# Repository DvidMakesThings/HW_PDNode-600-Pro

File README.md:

# PDNode-600 Pro  
## High-Performance USB PD Power Distribution Unit – 10" Rackmount

## Description  
[ENERGIS](https://github.com/DvidMakesThings/HW_10-In-Rack_PDU) is the 230V managed PDU project. PDNode-600 Pro is the modular DC/USB-C sibling for setups
where mains switching is not desired, but controllable, rack-friendly power output is still needed.

The PDNode-600 is a professional-grade, 600W USB Power Delivery Unit designed specifically for compact 10-inch rack systems, targeting embedded developers, homelab enthusiasts, test benches, and smart infrastructure. It delivers regulated, high-current power across 8x independent USB-C PD outputs and 4x fixed 5V USB-A outputs.

At the core of the PDNode platform is a centralized industrial-grade 24V/25A power supply, distributing regulated DC to dedicated per-port buck or buck-boost converters. Each USB-C port is managed by an MPQ4242-AEC1 PD controller, enabling clean, autonomous negotiation of power profiles up to 20V @ 3A or 5A with eMarker cable support. All power conversion, protection, and monitoring are designed to meet high reliability and safety standards.

The PDNode-600 Pro, by contrast, is built for remote-managed racks and headless environments, featuring Ethernet connectivity, a clean web-based UI, SNMP integration, and firmware updates via USB-C. Doing this by using [BladeCore-M54E](https://github.com/DvidMakesThings/HW_BladeCore-M54E)

## Web UI sneak peek

Interactive playground (dummy UI):
- https://dvidmakesthings.github.io/HW_PDNode-600-Pro/playground/

## Project timeline estimation

Status legend: ✅ Completed · 🟠 Ongoing · 🔵 Planned

| #  | Milestone                                      | Planned Start | Planned End | Status       | Notes |
|:--:|------------------------------------------------|---------------|-------------|--------------|-------|
| 1  | Architecture definition                        | 12-2025       | 01-2026     | ✅ Completed |       |
| 2  | Baseboard PCB design                           | 15-02-2026    | TBD         | ✅ Completed |       |
| 3  | PD card PCB design                             | 25-02-2026    | TBD         | ✅ Completed |       |
| 4  | Documentation                                  | 12-2025       | 2026.12     | 🟠 Ongoing   |       |
| 5  | PCB ordering                                   | 01-03-2026    | 31-03-2026  | ✅ Completed | Waiting for arrival |
| 6  | Prototyping and hardware bring-up              | 03-2026       | 30-04-2026  | 🟠 Ongoing   |       |
| 7  | Firmware bring-up (slot scan, mux, PD iface)   | 06-2026       | 11-2026     | 🔵 Planned   |       |
| 8  | Telemetry and status reporting                 | 06-2026       | 11-2026     | 🔵 Planned   |       |
| 9  | Validation (load, thermal, long-run)           | 06-2026       | 11-2026     | 🔵 Planned   |       |
| 10 | Integration and polishing                      | 06-2026       | 11-2026     | 🔵 Planned   |       |
| 11 | Release package and final docs                 | 11-2026       | 12-2026     | 🔵 Planned   |       |

## Specifications 

### Input
- **Input voltage:** 230 VAC, max 4A 
- **System topology:** 24V distribution on the baseboard, per-slot conversion on PD cards

### Output (per PD card / per slot)
- **8x independent USB-C PD source**:
  - 5V 3A (5A only with 5A e-marked cable)
  - 9V 3A (5A only with 5A e-marked cable)
  - 12V 3A (5A only with 5A e-marked cable)
  - 15V 3A (5A only with 5A e-marked cable)
  - 20V 3A (5A only with 5A e-marked cable)
  - (Total power output cannot exceed 600W)
- **4x USB-A source** up to **5V / 1A** per port (depending on configuration and limits)

---

## Features
- **8x independent USB-C PD source ports** (modular PD cards, one port per slot)
- **Per-port PD profiles**
- **Total system capability: up to 600W** (shared input power budget)
- **4x USB-A auxiliary outputs** (5V, 1A per port) for low-power devices
- **Ethernet connectivity** for control / monitoring
- **USB service interface** (debug, configuration, firmware update, or log access depending on implementation)
- **Per-port power monitoring** (current/voltage telemetry via onboard sensing)
- **Per-port status reporting** (PGOOD / fault indication, and software-readable status)
- **Hot-swappable slot concept** (cards can be replaced without redesigning the baseboard)

---

## Hardware architecture

### Baseboard
- 24V DC input from industrial power supply
- Power distribution to all slots (high-current bus)
- Slot connectors + slot management (card detect, enable, status aggregation)
- I2C fanout per slot (mux) for monitoring and controlling devices
- Ethernet interface for user interaction
- USB/service interface for debug/config/updates
- 4x USB-A outputs
- 8x USB-C PD outputs

### [BladeCore-M54E](https://github.com/DvidMakesThings/HW_BladeCore-M54E)
- RP2354B microcontroller
- External QSPI flash memory
- External I²C EEPROM
- 100BASE Ethernet via W5500
- Dual‑path USB connectivity with automatic source selection
- Onboard power regulation and defined power‑up sequencing
- Compact M.2 M-key form factor

### PD Card
- 1x USB-C PD source port (one card = one port)
- Local power conversion to generate VBUS from the 24V bus
- PD controller + USB-C port control signals (enable, reset, IRQ)
- Per-port current/voltage measurement
- Per-port power good / fault status output
- Optional ID EEPROM footprint (DNI) for traceability/calibration

## Schematics
The full schematics are available:
- **[Baseboard Schematics](src/PDF/SCH_PDNode_Baseboard_100.pdf)** 
- **[PDCard-4242 Schematics](src/PDF/SCH_PDCard-4242_100.pdf)**
- **[BladeCore-M54E Schematics](src/PDF/SCH_BladeCore-M54_100.pdf)**

PCB Documentation:
- **[Baseboard PCB](src/PDF/PCB_PDNode_Baseboard_100.pdf)** 
- **[PDCard-4242 PCB](src/PDF/PCB_PDCard-4242_100.pdf)**
 ****

---

## Development Phases (Hardware + Firmware)

| Hardware Phase                          | Status          | Firmware Phase                         | Status         |
| --------------------------------------- | --------------- | -------------------------------------- | -------------- |
| Architecture definition                 | ✅ Completed    | Slot scan concept (TCA9548A)           | 🔵 Planned     |
| Baseboard PCB Design                    | ✅ Completed    | I2C driver + mux control               | 🔵 Planned     |
| PD Card PCB Design                      | ✅ Completed    | INA219 monitoring                      | 🔵 Planned     |
| Documentation                           | 🟠 Ongoing      | PD controller interface (SPI + GPIO)   | 🔵 Planned     |
| PCB ordering                            | ✅ Completed    | Telemetry + status reporting           | 🔵 Planned     |
| Prototyping and Hardware Bring-up       | 🟠 Ongoing      | Bring-up scripts / debug tooling       | 🔵 Planned     |
| Validation (load, thermal, long-run)    | 🔵 Planned      | Error handling + fault reporting       | 🔵 Planned     |
| Production optimization                 | 🔵 Planned      | Integration and polishing              | 🔵 Planned     |

---

## Changelog 
#### Rev0.1.0:
- Initial design
- STUSB4710 controller + TPS552882

#### Rev1.0.0:
- Full redesign. STUSB4710 became EOL, need to use different PD controller
- New concept: modular Baseboard + PDCard architecture
- PDCard power stage (MPQ4242-AEC1)
- Baseboard: Per-slot I2C muxing (TCA9548A)
- Optional per-card EEPROM (not used, but capable)

<table>
  <tr>
    <td align="center">
      
      <br><b>PDCard Top</b>
    </td>
    <td align="center">
      
      <br><b>PDCard Bottom</b>
    </td>
  </tr>
  <tr>
    <td align="center" width="50%">
      
      <br><b>BladeCore-M54E Top</b>
    </td>
    <td align="center" width="50%">
      
      <br><b>BladeCore-M54E Bottom</b>
    </td>
  </tr>
  <tr>
    <td align="center">
      
      <br><b>BladeCore-M54E Top</b>
    </td>
    <td align="center">
      
      <br><b>BladeCore-M54E Bottom</b>
    </td>
  </tr>
</table>

## License
### Software Components
This project's software is licensed under the **GNU Affero General Public License v3.0 (AGPL-3.0)**.
See the [Software License](LICENSE-AGPL) file for details.

#### What AGPL-3.0 means:

- ✅ **You can** freely use, modify, and distribute this software
- ✅ **You can** use this project for personal, educational, or internal purposes
- ✅ **You can** contribute improvements back to this project

- ⚠️ **You must** share any modifications you make if you distribute the software
- ⚠️ **You must** release the source code if you run a modified version on a server that others interact with
- ⚠️ **You must** keep all copyright notices intact

- ❌ **You cannot** incorporate this code into proprietary software without sharing your source code
- ❌ **You cannot** use this project in a commercial product without either complying with AGPL or obtaining a different license

### Hardware Components
Hardware designs, schematics, and related documentation are licensed under the **Creative Commons Attribution-NonCommercial-ShareAlike 4.0 International License (CC BY-NC-SA 4.0 International License)**. See the [Hardware License](LICENSE-CC-BY-NC-SA) file for details.

#### What CC BY-NC-SA 4.0 means:

- ✅ **You can** study, modify, and distribute the hardware designs
- ✅ **You can** create derivative works for personal, educational, or non-commercial use
- ✅ **You can** build this project for your own personal use

- ⚠️ **You must** give appropriate credit and indicate if changes were made
- ⚠️ **You must** share any modifications under the same license terms
- ⚠️ **You must** include the original license and copyright notices

- ❌ **You cannot** use the designs for commercial purposes without explicit permission
- ❌ **You cannot** manufacture and sell products based on these designs without a commercial license
- ❌ **You cannot** create closed-source derivatives for commercial purposes
- ❌ **You cannot** use the designer's trademarks without permission

### Commercial & Enterprise Use

Commercial use of this project is prohibited without obtaining a separate commercial license. If you are interested in:

- Manufacturing and selling products based on these designs
- Incorporating these designs into commercial products
- Any other commercial applications

Please contact me through any of the channels listed in the [Contact](#contact) section to discuss commercial licensing arrangements. Commercial licenses are available with reasonable terms to support ongoing development.

## Contact

For questions or feedback:
- **Email:** [dvidmakesthings@gmail.com](mailto:dvidmakesthings@gmail.com)
- **GitHub:** [DvidMakesThings](https://github.com/DvidMakesThings)

## Contributing

Contributions are welcome! As this is an early-stage project, please reach out before 
making substantial changes:

1. Fork the repository
2. Create a feature branch (`git checkout -b feature/concept`)
3. Commit your changes (`git commit -m 'Add concept'`)
4. Push to the branch (`git push origin feature/concept`)
5. Open a Pull Request with a detailed description

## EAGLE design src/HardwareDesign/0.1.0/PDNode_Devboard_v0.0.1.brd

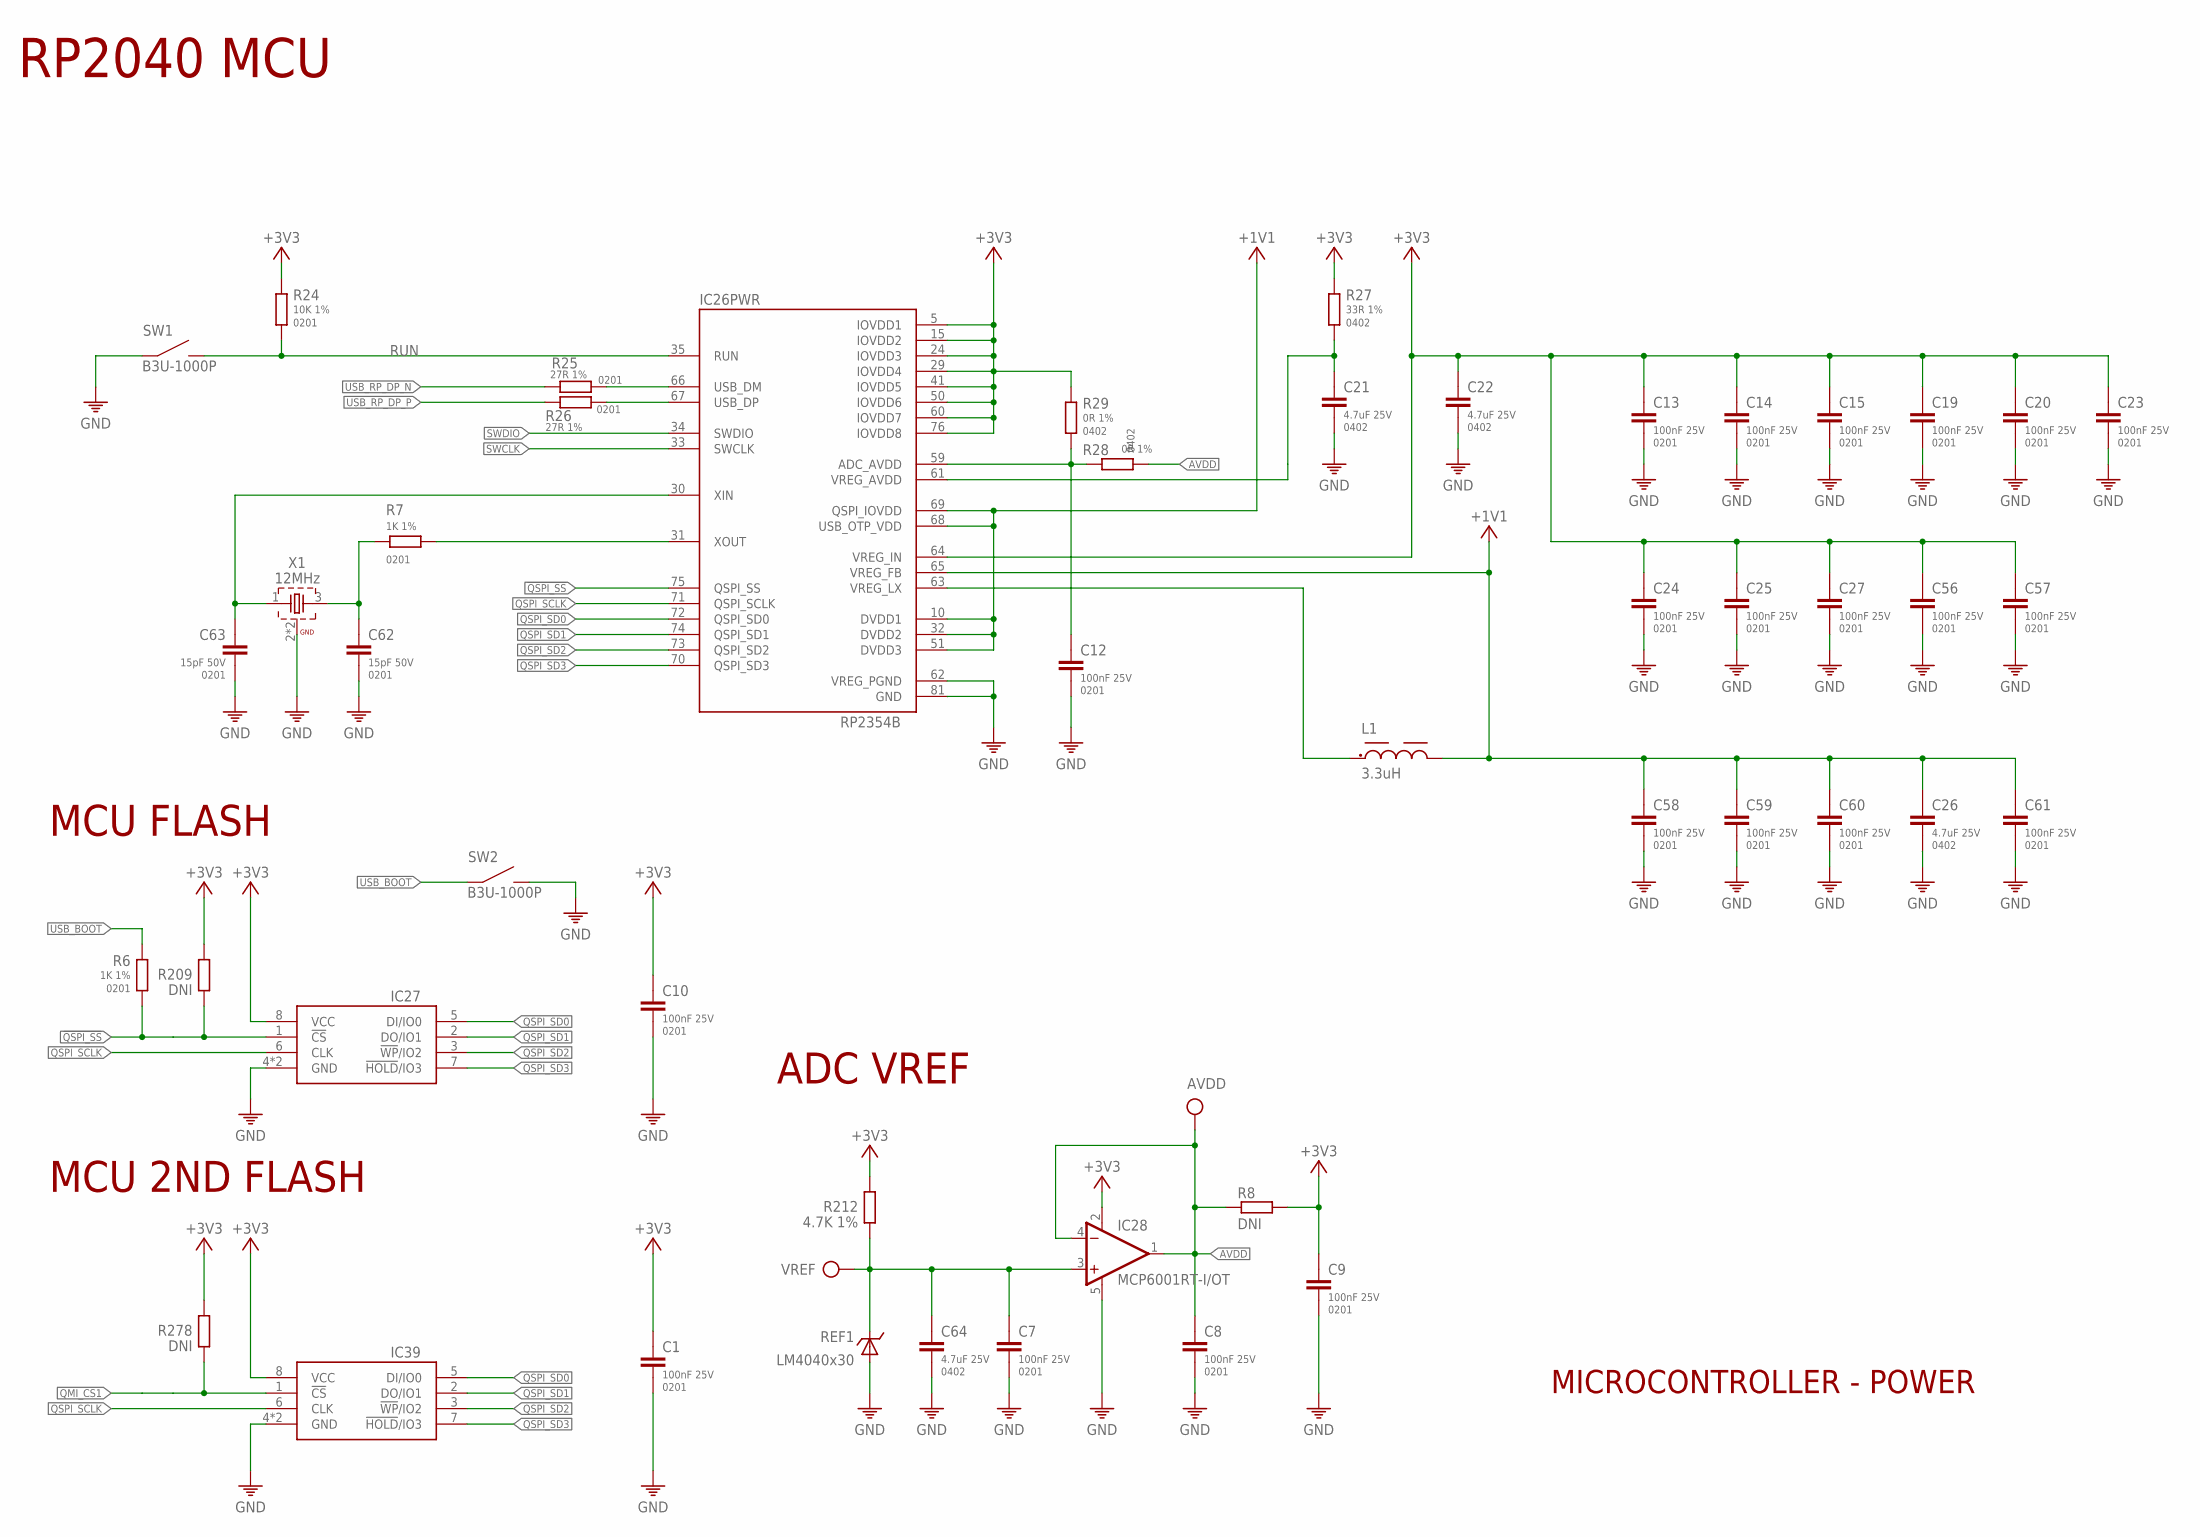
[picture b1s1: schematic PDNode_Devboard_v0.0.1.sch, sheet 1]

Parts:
AVDD: DNI; TP-ROUND
C1, C7, C8, C9, C10, C12, C13, C14, C15, C19, C20, C23, C24, C25, C27, C56, C57, C58, C59, C60, C61: 100nF 25V; 0201
C21, C22, C26, C64: 4.7uF 25V; 0402
C62, C63: 15pF 50V; 0201
IC26: RP2354B; QFN80-10X10
IC27, IC39: W25Q128JVPIQ; SON127P600X500X75-8N
IC28: MCP6001RT-I/OT; SOT23-5
L1: 3.3uH; 0805
R6, R7: 1K 1%; 0201
R8, R209, R278: DNI; R0201
R24: 10K 1%; 0201
R25, R26: 27R 1%; 0201
R27: 33R 1%; 0402
R28, R29: 0R 1%; 0402
R212: 4.7K 1%; 0201
REF1: LM4040x30; SOT23
SW1, SW2: B3U-1000P
VREF: DNI; TP-ROUND
X1: 12MHz; WE-XTAL_CFPX-180

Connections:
!QSPI_SS: IC26.75 (QSPI_SS), IC27.1 (!CS), R6.2, R209.1
+1V1: C26.1, C58.1, C59.1, C60.1, C61.1, IC26.10 (DVDD1), IC26.32 (DVDD2), IC26.51 (DVDD3), IC26.65 (VREG_FB), IC26.68 (USB_OTP_VDD), IC26.69 (QSPI_IOVDD), L1.2
+3V3: C1.1, C9.1, C10.1, C13.1, C14.1, C15.1, C19.1, C20.1, C22.1, C23.1, C24.1, C25.1, C27.1, C56.1, C57.1, IC26.5 (IOVDD1), IC26.15 (IOVDD2), IC26.24 (IOVDD3), IC26.29 (IOVDD4), IC26.41 (IOVDD5), IC26.50 (IOVDD6), IC26.60 (IOVDD7), IC26.64 (VREG_IN), IC26.76 (IOVDD8), IC27.8 (VCC), IC28.2 (V+), IC39.8 (VCC), R8.2, R24.1, R27.1, R29.1, R209.2, R212.2, R278.2; also elsewhere on the board
ADC_AVDD: C12.1, IC26.59 (ADC_AVDD), R28.1, R29.2
AVDD: AVDD.TP, C8.1, IC28.1 (OUT), IC28.4 (-IN), R8.1, R28.2
GND: C1.2, C7.2, C8.2, C9.2, C10.2, C12.2, C13.2, C14.2, C15.2, C19.2, C20.2, C21.2, C22.2, C23.2, C24.2, C25.2, C26.2, C27.2, C56.2, C57.2, C58.2, C59.2, C60.2, C61.2, C62.2, C63.2, C64.2, IC26.62 (VREG_PGND), IC26.81 (GND), IC27.4 (GND), IC27.PAD (GND), IC28.5 (V-), IC39.4 (GND), IC39.PAD (GND), REF1.2 (A), REF1.3 (A), SW1.1, SW2.2, X1.2 (GND), X1.4 (GND); also elsewhere on the board
unnamed: C21.1, IC26.61 (VREG_AVDD), R27.2
unnamed: IC26.63 (VREG_LX), L1.1
unnamed: C62.1, R7.1, X1.3 (2)
QMI_CS1: IC39.1 (!CS), R278.1; also elsewhere on the board
QSPI_SCLK: IC26.71 (QSPI_SCLK), IC27.6 (CLK), IC39.6 (CLK)
QSPI_SD0: IC26.72 (QSPI_SD0), IC27.5 (DI/IO0), IC39.5 (DI/IO0)
QSPI_SD1: IC26.74 (QSPI_SD1), IC27.2 (DO/IO1), IC39.2 (DO/IO1)
QSPI_SD2: IC26.73 (QSPI_SD2), IC27.3 (!WP!/IO2), IC39.3 (!WP!/IO2)
QSPI_SD3: IC26.70 (QSPI_SD3), IC27.7 (!HOLD!/IO3), IC39.7 (!HOLD!/IO3)
RP_XI: C63.1, IC26.30 (XIN), X1.1
RP_XO: IC26.31 (XOUT), R7.2
RUN: IC26.35 (RUN), R24.2, SW1.2; also elsewhere on the board
SWCLK: IC26.33 (SWCLK); also elsewhere on the board
SWDIO: IC26.34 (SWDIO); also elsewhere on the board
USB_BOOT: R6.1, SW2.1; also elsewhere on the board
USB_RPR_DP_N: IC26.66 (USB_DM), R25.2
USB_RPR_DP_P: IC26.67 (USB_DP), R26.2
USB_RP_DP_N: R25.1; also elsewhere on the board
USB_RP_DP_P: R26.1; also elsewhere on the board
VREF: C7.1, C64.1, IC28.3 (+IN), R212.1, REF1.1 (C), VREF.TP

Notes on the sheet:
RP2040 MCU
MCU FLASH
ADC VREF
MICROCONTROLLER - POWER
MCU 2ND FLASH

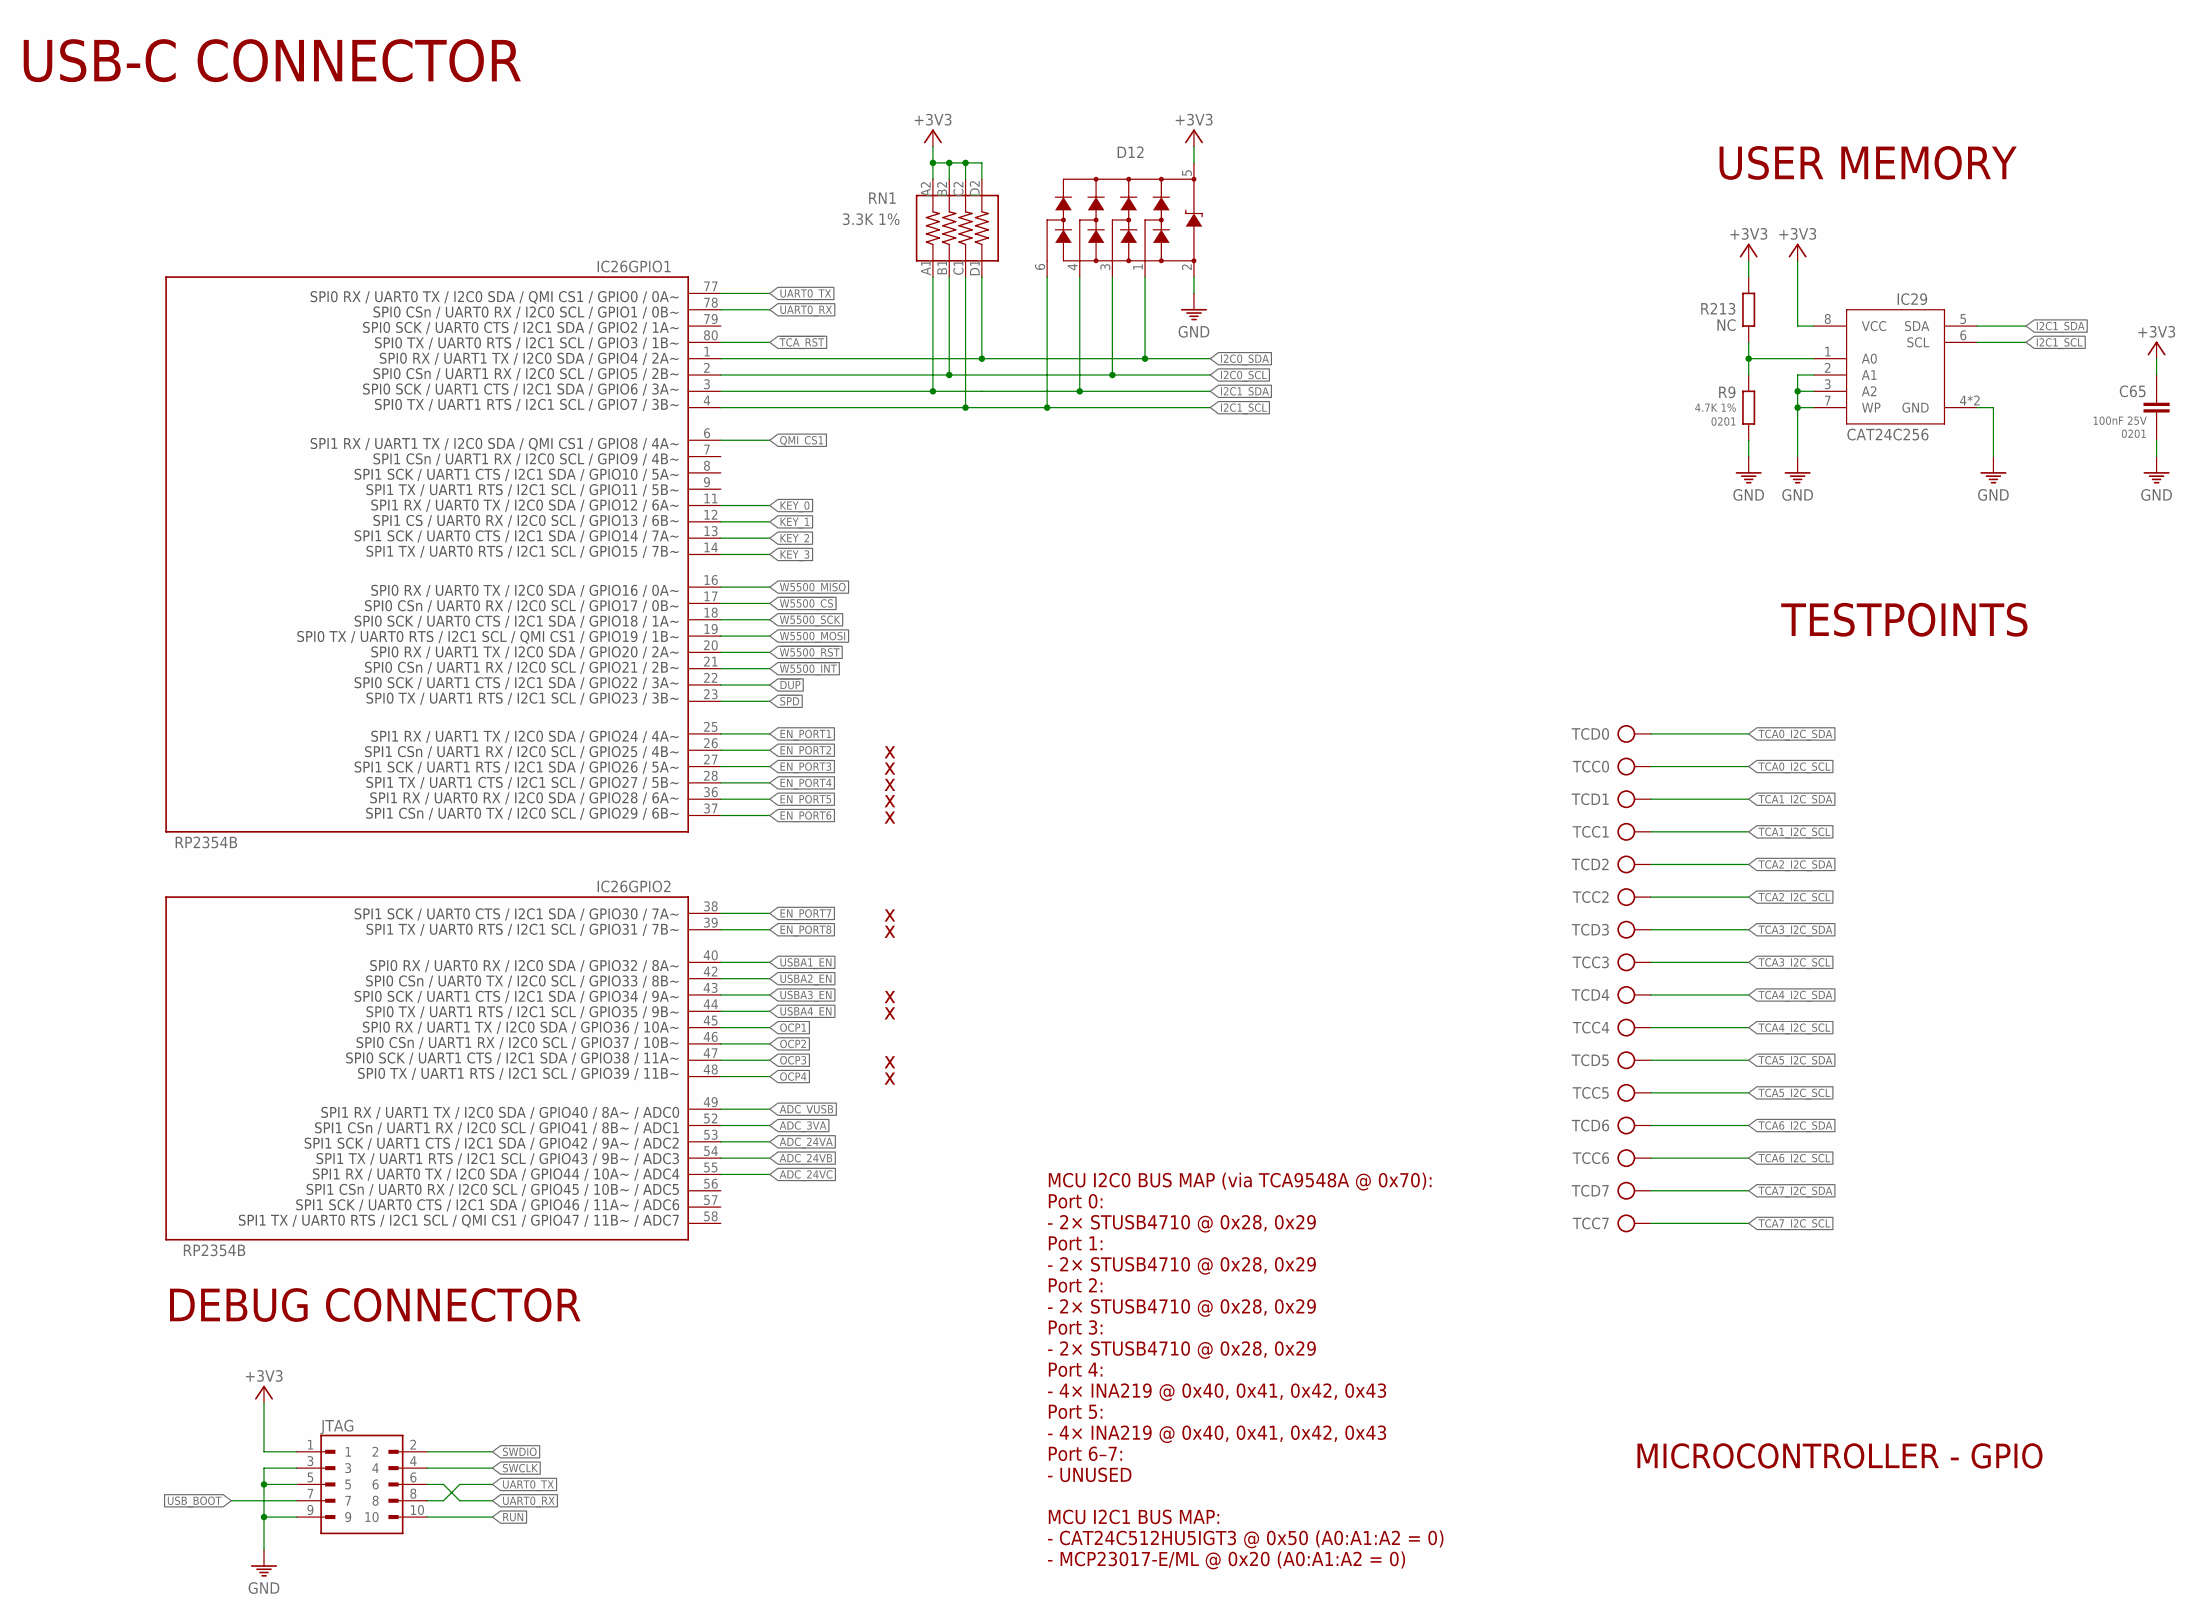
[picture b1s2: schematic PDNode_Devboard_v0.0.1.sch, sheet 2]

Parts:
C65: 100nF 25V; 0201
D12: HDMIULC6-4SC6Y; SOT23-6
IC26: RP2354B; QFN80-10X10
IC29: CAT24C256HU4IGT3; SON50P300X200X50-9T130X140N
JTAG: 3220_10_0300_00
R9: 4.7K 1%; 0201
R213: NC; R0201
RN1: 3.3K 1%; _0603X4-1206
TCC0, TCC1, TCC2, TCC3, TCC4, TCC5, TCC6, TCC7: DNI; TP-ROUND
TCD0, TCD1, TCD2, TCD3, TCD4, TCD5, TCD6, TCD7: DNI; TP-ROUND

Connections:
!DUP: IC26.22 (GPIO22); also elsewhere on the board
!SPD: IC26.23 (GPIO23); also elsewhere on the board
!TCA_RST: IC26.80 (GPIO3); also elsewhere on the board
!W5500_CS: IC26.17 (GPIO17); also elsewhere on the board
!W5500_INT: IC26.21 (GPIO21); also elsewhere on the board
!W5500_RST: IC26.20 (GPIO20); also elsewhere on the board
+3V3: C65.1, D12.5, IC29.8 (VCC), JTAG.1, R213.2, RN1.A2 (8), RN1.B2 (7), RN1.C2 (6), RN1.D2 (5); also elsewhere on the board
ADC_3VA: IC26.52 (GPIO41_ADC1)
ADC_24VA: IC26.53 (GPIO42_ADC2); also elsewhere on the board
ADC_24VB: IC26.54 (GPIO43_ADC3); also elsewhere on the board
ADC_24VC: IC26.55 (GPIO44_ADC4); also elsewhere on the board
ADC_VUSB: IC26.49 (GPIO40_ADC0); also elsewhere on the board
EN_PORT1: IC26.25 (GPIO24); also elsewhere on the board
EN_PORT2: IC26.26 (GPIO25)
EN_PORT3: IC26.27 (GPIO26)
EN_PORT4: IC26.28 (GPIO27)
EN_PORT5: IC26.36 (GPIO28)
EN_PORT6: IC26.37 (GPIO29)
EN_PORT7: IC26.38 (GPIO30)
EN_PORT8: IC26.39 (GPIO31)
GND: C65.2, D12.2, IC29.2 (A1), IC29.3 (A2), IC29.4 (GND), IC29.7 (WP), IC29.9 (GND), JTAG.3, JTAG.5, JTAG.9, R9.2; also elsewhere on the board
I2C0_SCL: D12.3, IC26.2 (GPIO5), RN1.B1 (2); also elsewhere on the board
I2C0_SDA: D12.1, IC26.1 (GPIO4), RN1.D1 (4); also elsewhere on the board
I2C1_SCL: D12.6, IC26.4 (GPIO7), IC29.6 (SCL), RN1.C1 (3); also elsewhere on the board
I2C1_SDA: D12.4, IC26.3 (GPIO6), IC29.5 (SDA), RN1.A1 (1); also elsewhere on the board
KEY_0: IC26.11 (GPIO12); also elsewhere on the board
KEY_1: IC26.12 (GPIO13); also elsewhere on the board
KEY_2: IC26.13 (GPIO14); also elsewhere on the board
KEY_3: IC26.14 (GPIO15); also elsewhere on the board
unnamed: IC29.1 (A0), R9.1, R213.1
OCP1: IC26.45 (GPIO36); also elsewhere on the board
OCP2: IC26.46 (GPIO37); also elsewhere on the board
OCP3: IC26.47 (GPIO38)
OCP4: IC26.48 (GPIO39)
QMI_CS1: IC26.6 (GPIO8); also elsewhere on the board
RUN: JTAG.10; also elsewhere on the board
SWCLK: JTAG.4; also elsewhere on the board
SWDIO: JTAG.2; also elsewhere on the board
TCA0_I2C_SCL: TCC0.TP; also elsewhere on the board
TCA0_I2C_SDA: TCD0.TP; also elsewhere on the board
TCA1_I2C_SCL: TCC1.TP; also elsewhere on the board
TCA1_I2C_SDA: TCD1.TP; also elsewhere on the board
TCA2_I2C_SCL: TCC2.TP; also elsewhere on the board
TCA2_I2C_SDA: TCD2.TP; also elsewhere on the board
TCA3_I2C_SCL: TCC3.TP; also elsewhere on the board
TCA3_I2C_SDA: TCD3.TP; also elsewhere on the board
TCA4_I2C_SCL: TCC4.TP; also elsewhere on the board
TCA4_I2C_SDA: TCD4.TP; also elsewhere on the board
TCA5_I2C_SCL: TCC5.TP; also elsewhere on the board
TCA5_I2C_SDA: TCD5.TP; also elsewhere on the board
TCA6_I2C_SCL: TCC6.TP; also elsewhere on the board
TCA6_I2C_SDA: TCD6.TP; also elsewhere on the board
TCA7_I2C_SCL: TCC7.TP; also elsewhere on the board
TCA7_I2C_SDA: TCD7.TP; also elsewhere on the board
UART0_RX: IC26.78 (GPIO1), JTAG.6
UART0_TX: IC26.77 (GPIO0), JTAG.8
USBA1_EN: IC26.40 (GPIO32); also elsewhere on the board
USBA2_EN: IC26.42 (GPIO33); also elsewhere on the board
USBA3_EN: IC26.43 (GPIO34)
USBA4_EN: IC26.44 (GPIO35)
USB_BOOT: JTAG.7; also elsewhere on the board
W5500_MISO: IC26.16 (GPIO16); also elsewhere on the board
W5500_MOSI: IC26.19 (GPIO19); also elsewhere on the board
W5500_SCK: IC26.18 (GPIO18); also elsewhere on the board

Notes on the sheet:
USB-C CONNECTOR
MCU I2C0 BUS MAP (via TCA9548A @ 0x70): Port 0: - 2× STUSB4710 @ 0x28, 0x29 Port 1: - 2× STUSB4710 @ 0x28, 0x29 Port 2: - 2× STUSB4710 @ 0x28, 0x29 Port 3: - 2× STUSB4710 @ 0x28, 0x29 Port 4: - 4× INA219 @ 0x40, 0x41, 0x42, 0x43 Port 5: - 4× INA219 @ 0x40, 0x41, 0x42, 0x43 Port 6–7: - UNUSED MCU I2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
USER MEMORY
MICROCONTROLLER - GPIO
DEBUG CONNECTOR
TESTPOINTS

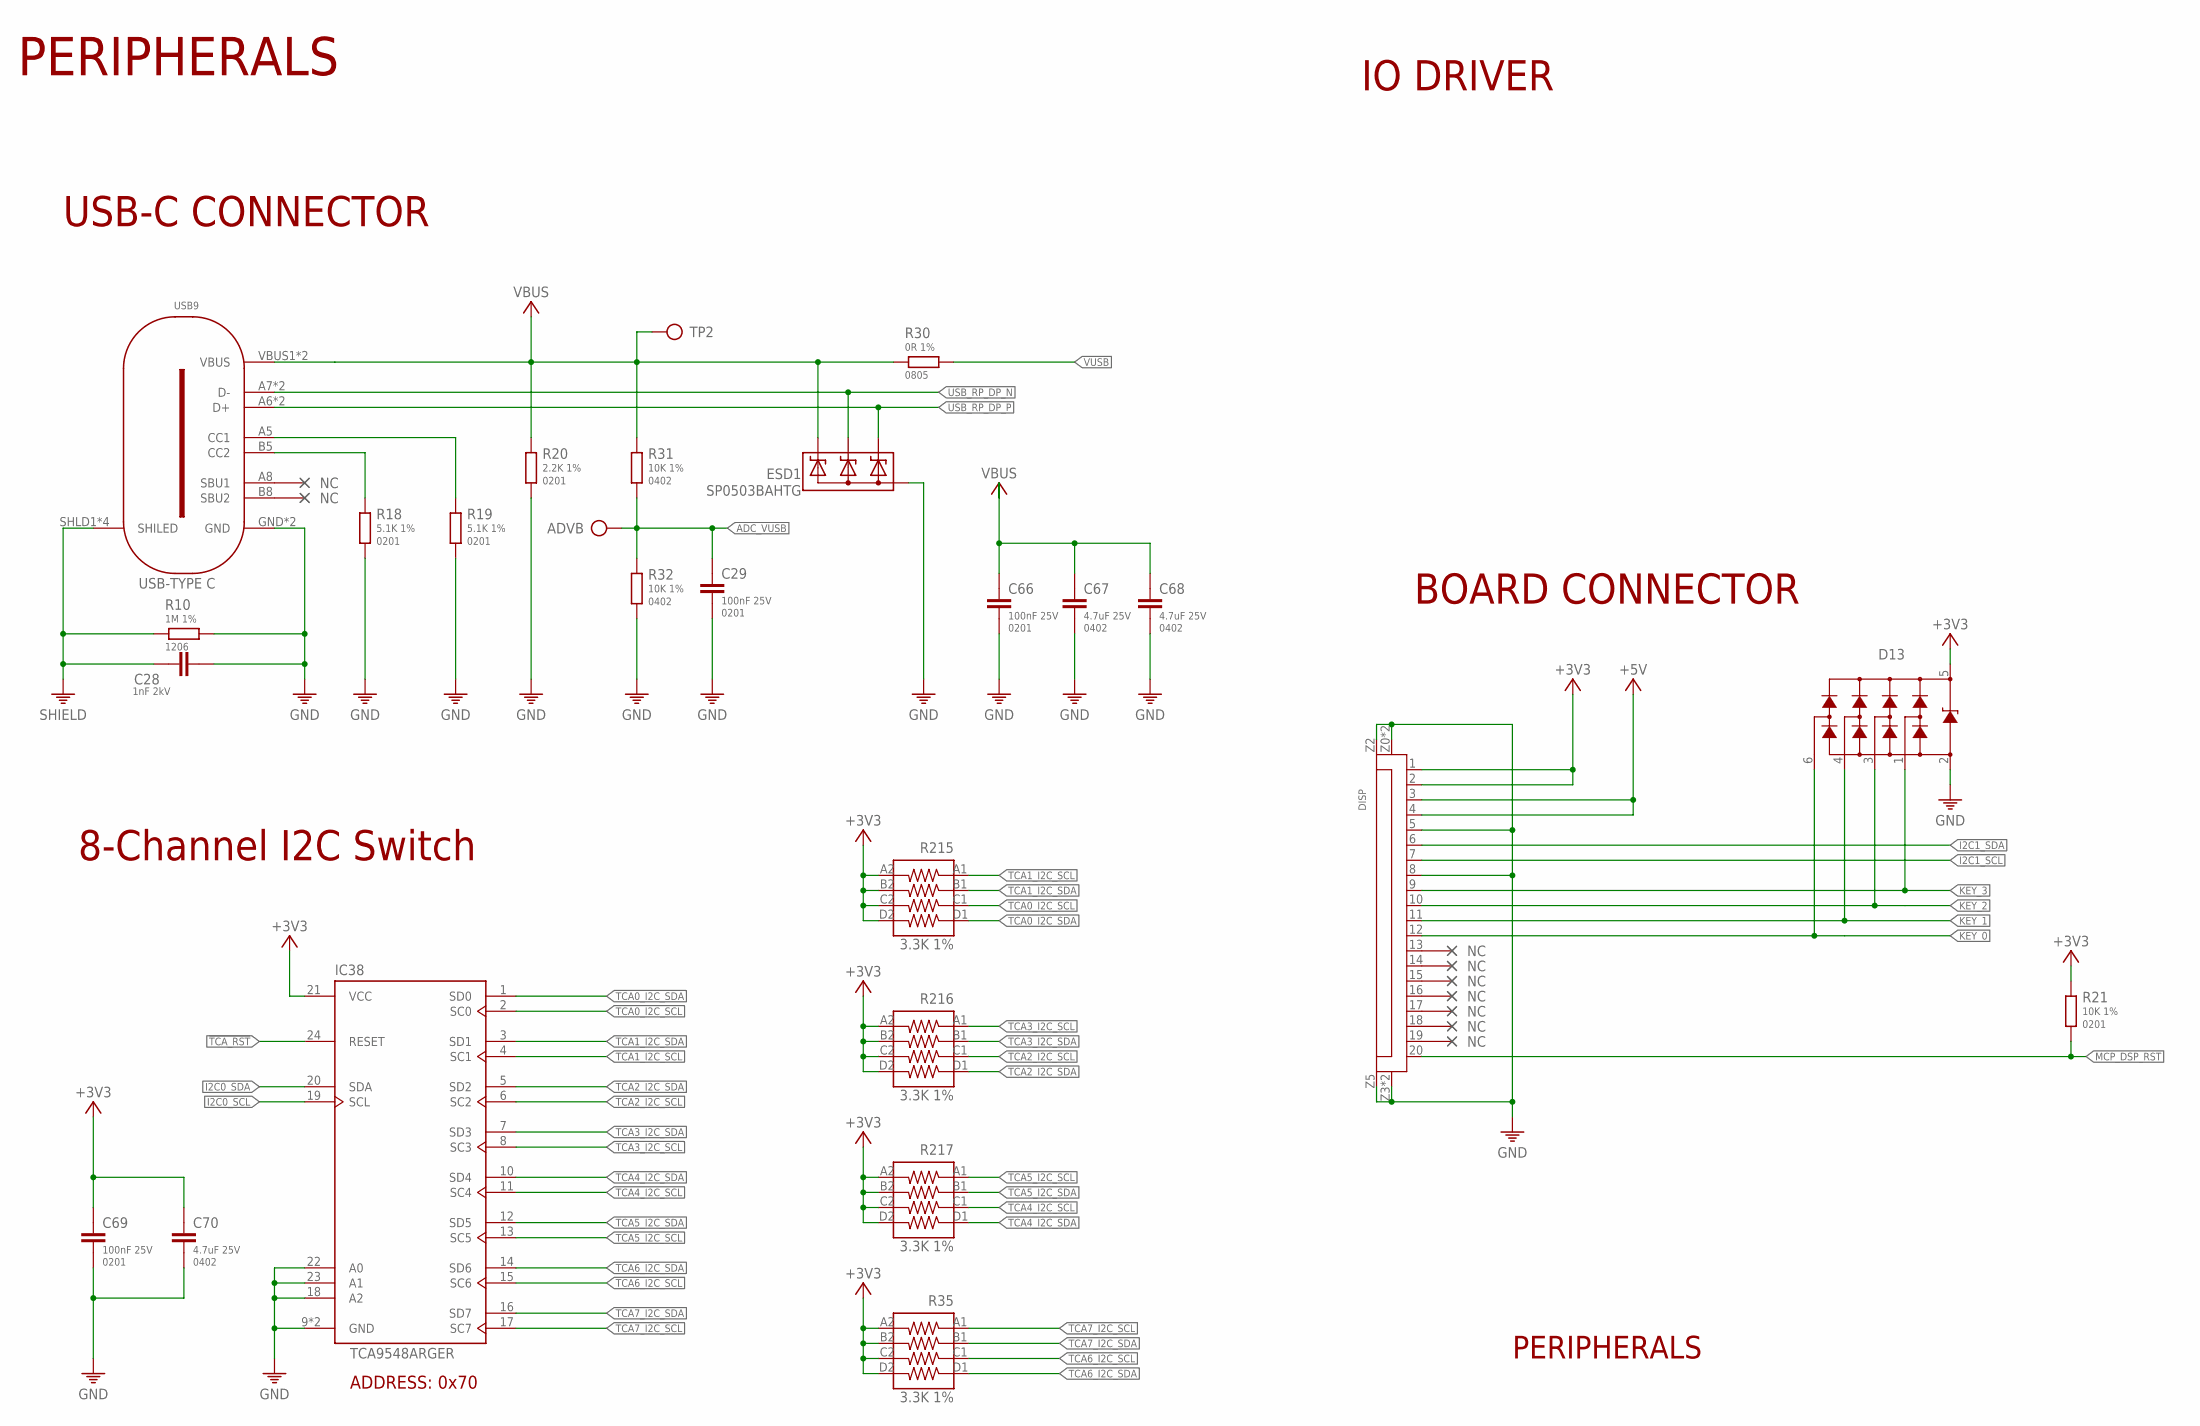
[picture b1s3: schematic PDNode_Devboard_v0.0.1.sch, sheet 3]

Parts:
ADVB: DNI; TP-ROUND
C28: 1nF 2kV; 1206
C29, C66, C69: 100nF 25V; 0201
C67, C68, C70: 4.7uF 25V; 0402
D13: HDMIULC6-4SC6Y; SOT23-6
DISP: AFC11-S20ICC-00; FPC20
ESD1: SP0503BAHTG; SOT143
IC38: TCA9548ARGER; QFN50P400X400X100-25T210N
R10: 1M 1%; 1206
R18, R19: 5.1K 1%; 0201
R20: 2.2K 1%; 0201
R21: 10K 1%; 0201
R30: 0R 1%; 0805
R31, R32: 10K 1%; 0402
R35, R215, R216, R217: 3.3K 1%; _0603X4-1206
TP2: DNI; TP-ROUND
USB9: USB-TYPE-C-018; USB-C

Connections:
!TCA_RST: IC38.24 (RESET); also elsewhere on the board
+3V3: C69.1, C70.1, D13.5, DISP.1, DISP.2, IC38.21 (VCC), R21.1, R35.A2 (8), R35.B2 (7), R35.C2 (6), R35.D2 (5), R215.A2 (8), R215.B2 (7), R215.C2 (6), R215.D2 (5), R216.A2 (8), R216.B2 (7), R216.C2 (6), R216.D2 (5), R217.A2 (8), R217.B2 (7), R217.C2 (6), R217.D2 (5); also elsewhere on the board
+5V: DISP.3, DISP.4
ADC_VUSB: ADVB.TP, C29.1, R31.2, R32.1; also elsewhere on the board
CC1: R19.1, USB9.A5 (CC1)
CC2: R18.1, USB9.B5 (CC2)
GND: C28.2, C29.2, C66.2, C67.2, C68.2, C69.2, C70.2, D13.2, DISP.5, DISP.8, DISP.Z0 (Z1), DISP.Z1, DISP.Z2, DISP.Z3, DISP.Z4 (Z3), DISP.Z5 (Z4), ESD1.1 (A), IC38.9 (GND), IC38.18 (A2), IC38.22 (A0), IC38.23 (A1), IC38.25 (GND), R10.2, R18.2, R19.2, R20.2, R32.2, USB9.GND, USB9.GND2 (GND); also elsewhere on the board
I2C0_SCL: IC38.19 (SCL); also elsewhere on the board
I2C0_SDA: IC38.20 (SDA); also elsewhere on the board
I2C1_SCL: DISP.7; also elsewhere on the board
I2C1_SDA: DISP.6; also elsewhere on the board
KEY_0: D13.6, DISP.12; also elsewhere on the board
KEY_1: D13.4, DISP.11; also elsewhere on the board
KEY_2: D13.3, DISP.10; also elsewhere on the board
KEY_3: D13.1, DISP.9; also elsewhere on the board
MCP_DSP_RST: DISP.20, R21.2
SHIELD: C28.1, R10.1, USB9.SHLD1 (SHILED), USB9.SHLD2 (SHILED), USB9.SHLD3 (SHILED), USB9.SHLD4 (SHILED); also elsewhere on the board
TCA0_I2C_SCL: IC38.2 (SC0), R215.C1 (3); also elsewhere on the board
TCA0_I2C_SDA: IC38.1 (SD0), R215.D1 (4); also elsewhere on the board
TCA1_I2C_SCL: IC38.4 (SC1), R215.A1 (1); also elsewhere on the board
TCA1_I2C_SDA: IC38.3 (SD1), R215.B1 (2); also elsewhere on the board
TCA2_I2C_SCL: IC38.6 (SC2), R216.C1 (3); also elsewhere on the board
TCA2_I2C_SDA: IC38.5 (SD2), R216.D1 (4); also elsewhere on the board
TCA3_I2C_SCL: IC38.8 (SC3), R216.A1 (1); also elsewhere on the board
TCA3_I2C_SDA: IC38.7 (SD3), R216.B1 (2); also elsewhere on the board
TCA4_I2C_SCL: IC38.11 (SC4), R217.C1 (3); also elsewhere on the board
TCA4_I2C_SDA: IC38.10 (SD4), R217.D1 (4); also elsewhere on the board
TCA5_I2C_SCL: IC38.13 (SC5), R217.A1 (1); also elsewhere on the board
TCA5_I2C_SDA: IC38.12 (SD5), R217.B1 (2); also elsewhere on the board
TCA6_I2C_SCL: IC38.15 (SC6), R35.C1 (3); also elsewhere on the board
TCA6_I2C_SDA: IC38.14 (SD6), R35.D1 (4); also elsewhere on the board
TCA7_I2C_SCL: IC38.17 (SC7), R35.A1 (1); also elsewhere on the board
TCA7_I2C_SDA: IC38.16 (SD7), R35.B1 (2); also elsewhere on the board
USB_RP_DP_N: ESD1.3 (C2), USB9.A7 (D-), USB9.B7 (D-); also elsewhere on the board
USB_RP_DP_P: ESD1.2 (C1), USB9.A6 (D+), USB9.B6 (D+); also elsewhere on the board
VBUS: C66.1, C67.1, C68.1, ESD1.4 (C3), R20.1, R30.1, R31.1, TP2.TP, USB9.VBUS1 (VBUS), USB9.VBUS2 (VBUS)
VUSB: R30.2

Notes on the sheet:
PERIPHERALS
USB-C CONNECTOR
8-Channel I2C Switch
ADDRESS: 0x70
IO DRIVER
BOARD CONNECTOR

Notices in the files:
parts and their libraries:
Wurth_Connectors_WR-TBL Rising Cage Clam: Copyright: Würth Elektronik
SparkFun-Aesthetics: Licensing: Creative Commons ShareAlike 4.0 International - https://creativecommons.org/licenses/by-sa/4.0
COPYRIGHT: Copyright (C) 2025 Ultra Librarian. All rights reserved.
